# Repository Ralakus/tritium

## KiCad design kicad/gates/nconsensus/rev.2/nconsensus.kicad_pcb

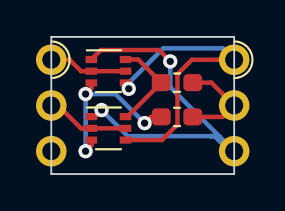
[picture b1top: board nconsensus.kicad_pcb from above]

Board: 2 copper layers, 10.2 x 7.6 mm, 6 parts (0 on the bottom side), 7 nets.

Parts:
J1, J2: Conn_01x03; Edge_Castellation_1x03_P2.54
Q1, Q2: BSS8402DW; SOT-363_SC-70-6
R1, R2: 12k; R_0603_1608Metric_Pad1.05x0.95mm_HandSolder

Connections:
A: J1.1, Q1.2, Q1.5
B: J1.2, Q2.2, Q2.5
unnamed: Q1.3, Q2.3, R1.1
unnamed: Q1.6, Q2.6, R2.2
Out: J2.2, R1.2, R2.1
Vdd: J2.1, Q1.4, Q2.4
Vss: J2.3, Q1.1, Q2.1

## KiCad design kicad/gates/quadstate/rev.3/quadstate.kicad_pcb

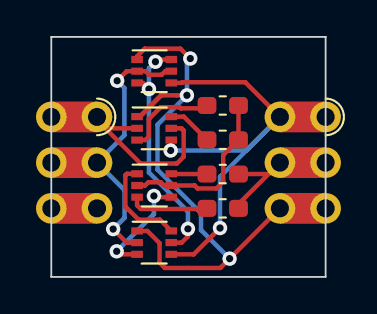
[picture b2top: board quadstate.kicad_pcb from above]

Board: 2 copper layers, 15.2 x 13.3 mm, 10 parts (0 on the bottom side), 13 nets.

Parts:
J1, J2: Conn_01x03; Hybrid_Castellation_1x03_P2.54
Q1, Q2, Q3, Q4: BSS8402DW; SOT-363_SC-70-6
R1, R2, R3, R4: 12k; R_0603_1608Metric_Pad1.05x0.95mm_HandSolder

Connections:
Gate: J1.2, Q1.2, Q1.5, Q2.2
In: J1.1, Q3.2, Q3.5
unnamed: Q1.3, Q1.6, Q2.5
unnamed: Q2.3, Q4.4
unnamed: Q2.6, Q4.1
unnamed: Q3.3, R1.1
unnamed: Q3.6, R2.2
unnamed: Q4.2, Q4.5, R1.2, R2.1
unnamed: Q4.3, R3.1
unnamed: Q4.6, R4.2
Out: J2.2, R3.2, R4.1
Vdd: J2.1, Q1.4, Q2.4, Q3.4
Vss: J2.3, Q1.1, Q2.1, Q3.1

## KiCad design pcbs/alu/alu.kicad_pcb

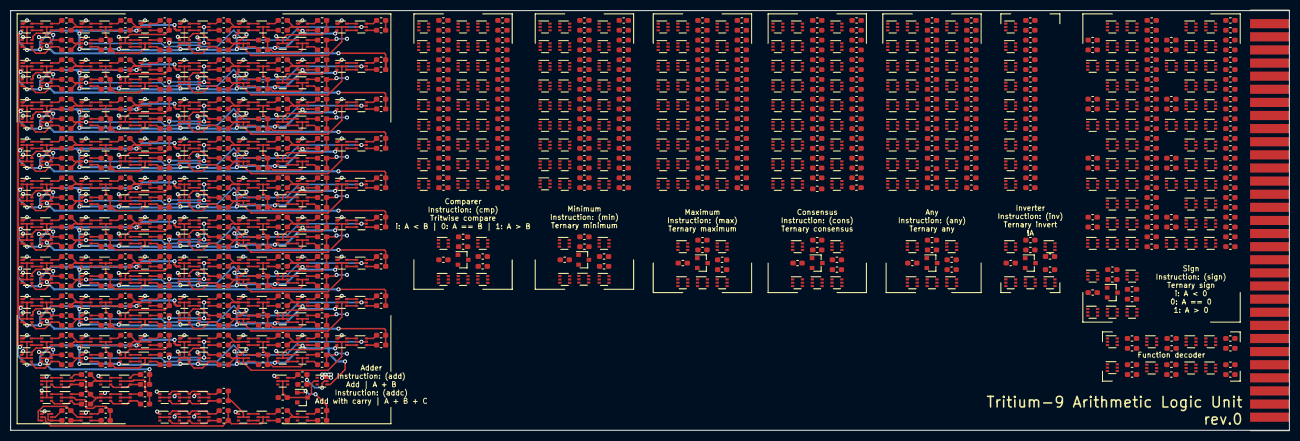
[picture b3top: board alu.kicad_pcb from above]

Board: 2 copper layers, 247.7 x 81.3 mm, 1037 parts (0 on the bottom side), 1030 nets.

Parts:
J1: Conn_02x31_Top_Bottom; BUS_AT_8bit
Q1, Q2, Q3, Q4, Q5, Q6, Q7, Q8, Q9, Q10, Q11, Q12, Q13, Q14, Q15, Q16, Q17, Q18, Q19, Q20, Q21, Q22, Q23, Q24, Q25, Q26, Q27, Q28, Q29, Q30, Q31, Q32, Q33, Q34, Q35, Q36, Q37, Q38, Q39, Q40, Q41, Q42, Q43, Q44, Q45, Q46, Q47, Q48, Q49, Q50, Q51, Q52, Q53, Q54, Q55, Q56, Q57, Q58, Q59, Q60, Q61, Q62, Q63, Q64, Q65, Q66, Q67, Q68, Q69, Q70, Q71, Q72, Q73, Q74, Q75, Q76, Q77, Q78, Q79, Q80, Q81, Q82, Q83, Q84, Q85, Q86, Q87, Q88, Q89, Q90, Q91, Q92, Q93, Q94, Q95, Q96, Q97, Q98, Q99, Q100, Q101, Q102, Q103, Q104, Q105, Q106, Q107, Q108, Q109, Q110, Q111, Q112, Q113, Q114, Q115, Q116, Q117, Q118, Q119, Q120, Q121, Q122, Q123, Q124, Q125, Q126, Q127, Q128, Q129, Q130, Q131, Q132, Q133, Q134, Q135, Q136, Q137, Q138, Q139, Q140, Q141, Q142, Q143, Q144, Q145, Q146, Q147, Q148, Q149, Q150, Q151, Q152, Q153, Q154, Q155, Q156, Q157, Q158, Q159, Q160, Q161, Q162, Q163, Q164, Q165, Q166, Q167, Q168, Q169, Q170, Q171, Q172, Q173, Q174, Q175, Q176, Q177, Q178, Q179, Q180, Q181, Q182, Q183, Q184, Q185, Q186, Q187, Q188, Q189, Q190, Q191, Q192, Q193, Q194, Q195, Q196, Q197, Q198, Q199, Q200, Q201, Q202, Q203, Q204, Q205, Q206, Q207, Q208, Q209, Q210, Q211, Q212, Q213, Q214, Q215, Q216, Q217, Q218, Q219, Q220, Q221, Q222, Q223, Q224, Q225, Q226, Q227, Q228, Q229, Q230, Q231, Q232, Q233, Q234, Q235, Q236, Q237, Q238, Q239, Q240, Q241, Q242, Q243, Q244, Q245, Q246, Q247, Q248, Q249, Q250, Q251, Q252, Q253, Q254, Q255, Q256, Q257, Q258, Q259, Q260, Q261, Q262, Q263, Q264, Q265, Q266, Q267, Q268, Q269, Q270, Q271, Q272, Q273, Q274, Q275, Q276, Q277, Q278, Q279, Q280, Q281, Q282, Q283, Q284, Q285, Q286, Q287, Q288, Q289, Q290, Q291, Q292, Q293, Q294, Q295, Q296, Q297, Q298, Q299, Q300, Q301, Q302, Q303, Q304, Q305, Q306, Q307, Q308, Q309, Q310, Q311, Q312, Q313, Q314, Q315, Q316, Q317, Q318, Q319, Q320, Q321, Q322, Q323, Q324, Q325, Q326, Q327, Q328, Q329, Q330, Q331, Q332, Q333, Q334, Q335, Q336, Q337, Q338, Q339, Q340, Q341, Q342, Q343, Q344, Q345, Q346, Q347, Q348, Q349, Q350, Q351, Q352, Q353, Q354, Q355, Q356, Q357, Q358, Q359, Q360, Q361, Q362, Q363, Q364, Q365, Q366, Q367, Q368, Q369, Q370, Q371, Q372, Q373, Q374, Q375, Q376, Q377, Q378, Q379, Q380, Q381, Q382, Q383, Q384, Q385, Q386, Q387, Q388, Q389, Q390, Q391, Q392, Q393, Q394, Q395, Q396, Q397, Q398, Q399, Q400, Q401, Q402, Q403, Q404, Q405, Q406, Q407, Q408, Q409, Q410, Q411, Q412, Q413, Q414, Q415, Q416, Q417, Q418, Q419, Q420, Q421, Q422, Q424, Q425, Q426, Q428, Q429, Q430, Q432, Q433, Q434, Q436, Q437, Q438, Q440, Q441, Q442, Q444, Q445, Q446, Q448, Q449, Q450, Q452, Q453, Q454, Q455, Q456, Q457, Q458, Q459, Q460, Q461, Q462, Q463, Q464, Q465, Q466, Q467, Q468, Q469, Q470: BSS8402DW; SOT-363_SC-70-6
Q423, Q427, Q431, Q435, Q439, Q443, Q447, Q451: 2N7002; SOT-23
R2, R3, R4, R5, R6, R7, R8, R9, R10, R11, R12, R13, R14, R15, R16, R17, R18, R19, R20, R21, R22, R23, R24, R25, R26, R27, R28, R29, R30, R31, R32, R33, R34, R35, R36, R37, R38, R39, R40, R41, R42, R43, R44, R45, R46, R47, R48, R49, R50, R51, R52, R53, R54, R55, R56, R57, R58, R59, R60, R61, R62, R63, R64, R65, R66, R67, R68, R69, R70, R71, R72, R73, R74, R75, R76, R77, R78, R79, R80, R81, R82, R83, R84, R85, R86, R87, R88, R89, R90, R91, R92, R93, R94, R95, R96, R97, R98, R99, R100, R101, R102, R103, R104, R105, R106, R107, R108, R109, R110, R111, R112, R113, R114, R115, R116, R117, R118, R119, R120, R121, R122, R123, R124, R125, R126, R127, R128, R129, R130, R131, R132, R133, R134, R135, R136, R137, R138, R139, R140, R141, R142, R143, R144, R145, R146, R147, R148, R149, R150, R151, R152, R153, R154, R155, R156, R157, R158, R159, R160, R161, R162, R163, R164, R165, R166, R167, R168, R169, R170, R171, R172, R173, R174, R175, R176, R177, R178, R179, R180, R181, R182, R183, R184, R185, R186, R187, R188, R189, R190, R191, R192, R193, R194, R195, R196, R197, R198, R199, R200, R201, R202, R203, R204, R205, R206, R207, R208, R209, R210, R211, R212, R213, R214, R215, R216, R217, R218, R219, R220, R221, R222, R223, R224, R225, R226, R227, R228, R229, R230, R231, R232, R233, R234, R235, R236, R237, R238, R239, R240, R241, R242, R243, R244, R245, R246, R247, R248, R249, R250, R251, R252, R253, R254, R255, R256, R257, R258, R259, R260, R261, R262, R263, R264, R265, R266, R267, R268, R269, R270, R271, R272, R273, R274, R275, R276, R277, R278, R279, R280, R281, R282, R283, R284, R285, R286, R287, R288, R289, R290, R291, R292, R293, R294, R295, R296, R297, R298, R299, R300, R301, R302, R303, R304, R305, R306, R307, R308, R309, R310, R311, R312, R313, R314, R315, R316, R317, R318, R319, R320, R321, R322, R323, R324, R325, R326, R327, R328, R329, R330, R331, R332, R333, R334, R335, R336, R337, R338, R339, R340, R341, R342, R343, R344, R345, R346, R347, R348, R349, R350, R351, R352, R353, R354, R355, R356, R357, R358, R359, R360, R361, R362, R363, R364, R365, R366, R367, R368, R369, R370, R371, R372, R373, R374, R375, R376, R377, R378, R379, R380, R381, R382, R383, R384, R385, R386, R387, R388, R389, R390, R391, R392, R393, R394, R395, R396, R397, R398, R399, R400, R401, R402, R403, R404, R405, R406, R407, R408, R409, R410, R411, R412, R413, R414, R415, R416, R417, R418, R419, R420, R421, R422, R423, R424, R425, R426, R427, R428, R429, R430, R431, R432, R433, R434, R435, R436, R437, R438, R439, R440, R441, R442, R443, R444, R445, R446, R447, R448, R449, R450, R451, R452, R453, R454, R455, R456, R457, R458, R459, R460, R461, R462, R463, R464, R465, R466, R467, R468, R469, R470, R471, R472, R473, R474, R475, R476, R477, R478, R479, R480, R481, R482, R483, R484, R485, R486, R487, R488, R489, R490, R491, R492, R493, R494, R495, R496, R497, R498, R499, R500, R501, R502, R503, R504, R505, R506, R507, R508, R517, R518, R519, R520, R521, R522, R523, R524, R525, R526, R527, R528, R529, R530, R531, R532, R533, R534, R535, R536, R537, R538, R539, R540, R541, R542, R543, R544, R545, R546, R547, R548, R549, R550, R551, R552, R553, R554, R555, R556, R557, R558, R560, R561, R562, R563, R564, R565, R566, R567, R568, R569, R570, R571, R572, R573, R574, R575: 12k; R_0603_1608Metric_Pad1.05x0.95mm_HandSolder
R559: 470k; R_0603_1608Metric_Pad1.05x0.95mm_HandSolder

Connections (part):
/FnA0: Q5.6, Q417.2, Q417.5, Q454.2, Q454.5, Q456.2, Q456.5, Q458.2, Q458.5, R439.1
/FnA1: Q460.2, Q460.5, Q462.2, Q462.5, Q464.2, Q464.5, R528.1, R529.2
/FnA2: Q412.2, Q412.5, Q466.2, Q466.5, Q468.2, Q468.5, Q470.2, Q470.5, R452.1, R517.2
/FnB0: Q4.6, Q416.2, Q416.5, Q421.2, Q421.5, Q433.2, Q433.5, Q445.2, Q445.5, R5.1
/FnB1: Q425.2, Q425.5, Q437.2, Q437.5, Q449.2, Q449.5, R526.1, R527.2
/FnB2: Q411.2, Q411.5, Q429.2, Q429.5, Q441.2, Q441.5, Q453.2, Q453.5, R450.1, R451.2
/adder/CarryIn: Q12.2, Q12.5, Q15.2, Q15.5, R530.1, R531.2
/adder/Vdd: Q6.3, Q7.3, Q8.3, Q9.3, Q10.3, Q11.3, Q12.3, Q13.3, Q14.3, Q18.3, Q19.3, Q20.3, Q21.3, Q22.3, Q23.3, Q27.3, Q28.3, Q29.3, Q30.3, Q31.3, Q32.3, Q36.3, Q37.3, Q38.3, Q39.3, Q40.3, Q41.3, Q42.3, Q43.3, Q44.3, Q48.3, Q49.3, Q50.3, Q51.3, Q52.3, Q53.3, Q57.3, Q58.3, Q59.3, Q60.3, Q61.3, Q62.3, Q66.3, Q67.3, Q68.3, Q72.3, Q73.3, Q74.3, Q75.3, Q76.3, Q77.3, Q78.3, Q79.3, Q80.3, Q84.3, Q85.3, Q86.3, Q87.3, Q88.3, Q89.3, Q93.3, Q94.3, Q95.3, Q96.3, Q97.3, Q98.3, Q102.3, Q103.3, Q104.3, Q105.3, Q106.3, Q107.3, Q108.3, Q109.3, Q110.3, Q114.3, Q115.3, Q116.3, Q117.3, Q118.3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
/adder/Vss: Q6.1, Q7.1, Q8.1, Q9.1, Q10.1, Q11.1, Q12.1, Q13.1, Q14.1, Q18.1, Q19.1, Q20.1, Q21.1, Q22.1, Q23.1, Q27.1, Q28.1, Q29.1, Q30.1, Q31.1, Q32.1, Q36.1, Q37.1, Q38.1, Q39.1, Q40.1, Q41.1, Q42.1, Q43.1, Q44.1, Q48.1, Q49.1, Q50.1, Q51.1, Q52.1, Q53.1, Q57.1, Q58.1, Q59.1, Q60.1, Q61.1, Q62.1, Q66.1, Q67.1, Q68.1, Q72.1, Q73.1, Q74.1, Q75.1, Q76.1, Q77.1, Q78.1, Q79.1, Q80.1, Q84.1, Q85.1, Q86.1, Q87.1, Q88.1, Q89.1, Q93.1, Q94.1, Q95.1, Q96.1, Q97.1, Q98.1, Q102.1, Q103.1, Q104.1, Q105.1, Q106.1, Q107.1, Q108.1, Q109.1, Q110.1, Q114.1, Q115.1, Q116.1, Q117.1, Q118.1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
/any/Vdd: Q312.3, Q314.3, Q315.3, Q317.3, Q318.3, Q320.3, Q321.3, Q323.3, Q324.3, Q326.3, Q327.3, Q329.3, Q330.3, Q332.3, Q333.3, Q335.3, Q336.3, Q338.3, Q442.4
/any/Vss: Q312.1, Q314.1, Q315.1, Q317.1, Q318.1, Q320.1, Q321.1, Q323.1, Q324.1, Q326.1, Q327.1, Q329.1, Q330.1, Q332.1, Q333.1, Q335.1, Q336.1, Q338.1, Q442.6
/compare/Vdd: Q258.3, Q259.3, Q260.3, Q261.3, Q262.3, Q263.3, Q264.3, Q265.3, Q266.3, Q267.3, Q268.3, Q269.3, Q270.3, Q271.3, Q272.3, Q273.3, Q274.3, Q275.3, Q276.3, Q277.3, Q278.3, Q279.3, Q280.3, Q281.3, Q282.3, Q283.3, Q284.3, Q426.4
/compare/Vss: Q258.1, Q259.1, Q260.1, Q261.1, Q262.1, Q263.1, Q264.1, Q265.1, Q266.1, Q267.1, Q268.1, Q269.1, Q270.1, Q271.1, Q272.1, Q273.1, Q274.1, Q275.1, Q276.1, Q277.1, Q278.1, Q279.1, Q280.1, Q281.1, Q282.1, Q283.1, Q284.1, Q426.6
/consensus/Vdd: Q285.3, Q286.3, Q287.3, Q288.3, Q289.3, Q290.3, Q291.3, Q292.3, Q293.3, Q294.3, Q295.3, Q296.3, Q297.3, Q298.3, Q299.3, Q300.3, Q301.3, Q302.3, Q303.3, Q304.3, Q305.3, Q306.3, Q307.3, Q308.3, Q309.3, Q310.3, Q311.3, Q438.4
/consensus/Vss: Q285.1, Q286.1, Q287.1, Q288.1, Q289.1, Q290.1, Q291.1, Q292.1, Q293.1, Q294.1, Q295.1, Q296.1, Q297.1, Q298.1, Q299.1, Q300.1, Q301.1, Q302.1, Q303.1, Q304.1, Q305.1, Q306.1, Q307.1, Q308.1, Q309.1, Q310.1, Q311.1, Q438.6
/inverter/Vdd: Q339.3, Q340.3, Q341.3, Q342.3, Q343.3, Q344.3, Q345.3, Q346.3, Q347.3, Q446.4
/inverter/Vss: Q339.1, Q340.1, Q341.1, Q342.1, Q343.1, Q344.1, Q345.1, Q346.1, Q347.1, Q446.6
/max/Vdd: Q231.3, Q233.3, Q234.3, Q236.3, Q237.3, Q239.3, Q240.3, Q242.3, Q243.3, Q245.3, Q246.3, Q248.3, Q249.3, Q251.3, Q252.3, Q254.3, Q255.3, Q257.3, Q434.4
/max/Vss: Q231.1, Q232.1, Q233.1, Q234.1, Q235.1, Q236.1, Q237.1, Q238.1, Q239.1, Q240.1, Q241.1, Q242.1, Q243.1, Q244.1, Q245.1, Q246.1, Q247.1, Q248.1, Q249.1, Q250.1, Q251.1, Q252.1, Q253.1, Q254.1, Q255.1, Q256.1, Q257.1, Q434.6
/min/Vdd: Q204.3, Q205.3, Q206.3, Q207.3, Q208.3, Q209.3, Q210.3, Q211.3, Q212.3, Q213.3, Q214.3, Q215.3, Q216.3, Q217.3, Q218.3, Q219.3, Q220.3, Q221.3, Q222.3, Q223.3, Q224.3, Q225.3, Q226.3, Q227.3, Q228.3, Q229.3, Q230.3, Q430.4
/min/Vss: Q204.1, Q206.1, Q207.1, Q209.1, Q210.1, Q212.1, Q213.1, Q215.1, Q216.1, Q218.1, Q219.1, Q221.1, Q222.1, Q224.1, Q225.1, Q227.1, Q228.1, Q230.1, Q430.6
/sign/Vdd: Q351.3, Q352.3, Q353.3, Q354.3, Q356.3, Q357.3, Q358.3, Q359.3, Q360.3, Q361.3, Q362.3, Q363.3, Q365.3, Q366.3, Q367.3, Q368.3, Q373.3, Q374.3, Q375.3, Q376.3, Q381.3, Q382.3, Q383.3, Q384.3, Q385.3, Q386.3, Q387.3, Q388.3, Q391.3, Q392.3, Q395.3, Q396.3, Q397.3, Q398.3, Q400.3, Q402.3, Q403.3, Q404.3, Q405.3, Q407.3, Q450.4
/sign/Vss: Q351.1, Q352.1, Q353.1, Q354.1, Q356.1, Q357.1, Q358.1, Q359.1, Q360.1, Q361.1, Q362.1, Q363.1, Q365.1, Q366.1, Q367.1, Q368.1, Q373.1, Q374.1, Q375.1, Q376.1, Q381.1, Q382.1, Q383.1, Q384.1, Q385.1, Q386.1, Q387.1, Q388.1, Q391.1, Q392.1, Q395.1, Q396.1, Q397.1, Q398.1, Q400.1, Q402.1, Q403.1, Q404.1, Q405.1, Q407.1, Q450.6
A0: J1.40, Q6.2, Q6.5, Q7.2, Q7.5, Q230.2, Q230.5, Q257.2, Q257.5, Q283.2, Q283.5, Q311.2, Q311.5, Q338.2, Q338.5, Q347.2, Q347.5, Q402.2, Q402.5, Q406.2, Q406.5
A1: J1.39, Q72.2, Q72.5, Q73.2, Q73.5, Q227.2, Q227.5, Q254.2, Q254.5, Q280.2, Q280.5, Q308.2, Q308.5, Q335.2, Q335.5, Q346.2, Q346.5, Q354.2, Q354.5, Q372.2, Q372.5
A2: J1.38, Q138.2, Q138.5, Q139.2, Q139.5, Q224.2, Q224.5, Q251.2, Q251.5, Q277.2, Q277.5, Q305.2, Q305.5, Q332.2, Q332.5, Q345.2, Q345.5, Q362.2, Q362.5, Q368.2, Q368.5
A3: J1.37, Q8.2, Q8.5, Q9.2, Q9.5, Q221.2, Q221.5, Q248.2, Q248.5, Q274.2, Q274.5, Q302.2, Q302.5, Q329.2, Q329.5, Q344.2, Q344.5, Q353.2, Q353.5, Q371.2, Q371.5
A4: J1.36, Q74.2, Q74.5, Q75.2, Q75.5, Q218.2, Q218.5, Q245.2, Q245.5, Q271.2, Q271.5, Q299.2, Q299.5, Q326.2, Q326.5, Q343.2, Q343.5, Q360.2, Q360.5, Q367.2, Q367.5
A5: J1.35, Q140.2, Q140.5, Q141.2, Q141.5, Q215.2, Q215.5, Q242.2, Q242.5, Q268.2, Q268.5, Q296.2, Q296.5, Q323.2, Q323.5, Q342.2, Q342.5, Q352.2, Q352.5, Q370.2, Q370.5
A6: J1.34, Q10.2, Q10.5, Q11.2, Q11.5, Q212.2, Q212.5, Q239.2, Q239.5, Q265.2, Q265.5, Q293.2, Q293.5, Q320.2, Q320.5, Q341.2, Q341.5, Q358.2, Q358.5, Q366.2, Q366.5
A7: J1.33, Q76.2, Q76.5, Q77.2, Q77.5, Q209.2, Q209.5, Q236.2, Q236.5, Q262.2, Q262.5, Q290.2, Q290.5, Q317.2, Q317.5, Q340.2, Q340.5, Q351.2, Q351.5, Q369.2, Q369.5
A8: J1.32, Q142.2, Q142.5, Q143.2, Q143.5, Q206.2, Q206.5, Q233.2, Q233.5, Q259.2, Q259.5, Q287.2, Q287.5, Q314.2, Q314.5, Q339.2, Q339.5, Q356.2, Q356.5, Q365.2, Q365.5
B0: J1.49, Q36.2, Q36.5, Q37.2, Q37.5, Q229.2, Q229.5, Q256.2, Q256.5, Q284.2, Q284.5, Q310.2, Q310.5, Q337.2, Q337.5
B1: J1.48, Q102.2, Q102.5, Q103.2, Q103.5, Q226.2, Q226.5, Q253.2, Q253.5, Q281.2, Q281.5, Q307.2, Q307.5, Q334.2, Q334.5
B2: J1.47, Q168.2, Q168.5, Q169.2, Q169.5, Q223.2, Q223.5, Q250.2, Q250.5, Q278.2, Q278.5, Q304.2, Q304.5, Q331.2, Q331.5
B3: J1.46, Q38.2, Q38.5, Q39.2, Q39.5, Q220.2, Q220.5, Q247.2, Q247.5, Q275.2, Q275.5, Q301.2, Q301.5, Q328.2, Q328.5
B4: J1.45, Q104.2, Q104.5, Q105.2, Q105.5, Q217.2, Q217.5, Q244.2, Q244.5, Q272.2, Q272.5, Q298.2, Q298.5, Q325.2, Q325.5
B5: J1.44, Q170.2, Q170.5, Q171.2, Q171.5, Q214.2, Q214.5, Q241.2, Q241.5, Q269.2, Q269.5, Q295.2, Q295.5, Q322.2, Q322.5
B6: J1.43, Q40.2, Q40.5, Q41.2, Q41.5, Q211.2, Q211.5, Q238.2, Q238.5, Q266.2, Q266.5, Q292.2, Q292.5, Q319.2, Q319.5
B7: J1.42, Q106.2, Q106.5, Q107.2, Q107.5, Q208.2, Q208.5, Q235.2, Q235.5, Q263.2, Q263.5, Q289.2, Q289.5, Q316.2, Q316.5
B8: J1.41, Q172.2, Q172.5, Q173.2, Q173.5, Q205.2, Q205.5, Q232.2, Q232.5, Q260.2, Q260.5, Q286.2, Q286.5, Q313.2, Q313.5
CarryIn: J1.30, Q3.2, Q3.5, Q355.2, Q355.5
CarryOut: J1.31, R239.1, R240.2
Fn0: J1.58, Q4.2, Q4.5
Fn1: J1.57, Q5.2, Q5.5
GND: J1.20, J1.51, Q1.5, Q423.2, Q427.2, Q431.2, Q435.2, Q439.2, Q443.2, Q447.2, Q451.2, R559.1
unnamed: Q1.2, Q414.2, Q414.5, R535.1, R536.2
unnamed: Q1.3, Q2.2, Q2.5, R559.2
unnamed: Q1.4, Q1.6, R558.1
unnamed: Q2.4, R2.2
unnamed: Q2.6, R3.1
unnamed: Q3.4, Q348.4, R440.2
unnamed: Q3.6, Q348.1
unnamed: Q10.4, Q17.3
unnamed: Q10.6, Q17.1
unnamed: Q11.4, Q14.4, R11.2
unnamed: Q11.6, Q14.6, R12.1
unnamed: Q7.4, Q12.4, R7.2
unnamed: Q7.6, Q12.6, R8.1
unnamed: Q13.2, Q13.5, Q16.2, Q16.5, R235.1, R236.2
unnamed: Q9.4, Q13.4, R9.2
unnamed: Q9.6, Q13.6, R10.1
unnamed: Q14.2, Q14.5, Q17.2, Q17.5, R237.1, R238.2
unnamed: Q6.6, Q15.1
unnamed: Q6.4, Q15.3
unnamed: Q15.4, R13.2
unnamed: Q15.6, R14.1
unnamed: Q8.6, Q16.1
unnamed: Q8.4, Q16.3
unnamed: Q16.4, R15.2
unnamed: Q16.6, R16.1
unnamed: Q17.4, R17.2
unnamed: Q17.6, R18.1
unnamed: Q18.2, Q18.5, Q69.2, Q69.5, R7.1, R8.2
unnamed: Q18.4, R19.2
unnamed: Q18.6, R20.1
unnamed: Q19.2, Q19.5, Q70.2, Q70.5, R9.1, R10.2
unnamed: Q19.4, R21.2
unnamed: Q19.6, R22.1
unnamed: Q20.2, Q20.5, Q71.2, Q71.5, R11.1, R12.2
unnamed: Q20.4, R23.2
unnamed: Q20.6, R24.1
unnamed: Q21.2, Q21.5, R13.1, R14.2
unnamed: Q21.4, Q24.3
unnamed: Q21.6, Q24.1
unnamed: Q22.2, Q22.5, R15.1, R16.2
unnamed: Q22.4, Q25.3
unnamed: Q22.6, Q25.1
unnamed: Q23.2, Q23.5, R17.1, R18.2
unnamed: Q23.4, Q26.3
unnamed: Q23.6, Q26.1
unnamed: Q24.2, Q24.5, Q33.2, Q33.5, R19.1, R20.2
unnamed: Q24.4, R25.2
unnamed: Q24.6, R26.1
unnamed: Q25.2, Q25.5, Q34.2, Q34.5, R21.1, R22.2
unnamed: Q25.4, R27.2
unnamed: Q25.6, R28.1
unnamed: Q26.2, Q26.5, Q35.2, Q35.5, R23.1, R24.2
unnamed: Q26.4, R29.2
unnamed: Q26.6, R30.1
unnamed: Q27.2, Q27.5, R25.1, R26.2
unnamed: Q27.4, R31.2
unnamed: Q27.6, R32.1
unnamed: Q28.2, Q28.5, R27.1, R28.2
unnamed: Q28.4, R33.2
unnamed: Q28.6, R34.1
unnamed: Q29.2, Q29.5, R29.1, R30.2
unnamed: Q29.4, R35.2
unnamed: Q29.6, R36.1
unnamed: Q30.2, Q30.5, R31.1, R32.2
unnamed: Q30.4, Q33.3
unnamed: Q30.6, Q33.1
unnamed: Q31.2, Q31.5, R33.1, R34.2
unnamed: Q31.4, Q34.3
unnamed: Q31.6, Q34.1
unnamed: Q32.2, Q32.5, R35.1, R36.2
unnamed: Q32.4, Q35.3
unnamed: Q32.6, Q35.1
unnamed: Q33.4, R37.2
unnamed: Q33.6, R38.1
unnamed: Q34.4, R39.2
unnamed: Q34.6, R40.1
unnamed: Q35.4, R41.2
unnamed: Q35.6, R42.1
unnamed: Q36.4, Q45.3
unnamed: Q36.6, Q45.1
unnamed: Q37.4, Q42.4, R43.2
unnamed: Q37.6, Q42.6, R44.1
unnamed: Q38.4, Q46.3
unnamed: Q38.6, Q46.1
unnamed: Q39.4, Q43.4, R45.2
unnamed: Q39.6, Q43.6, R46.1
unnamed: Q40.4, Q47.3
unnamed: Q40.6, Q47.1
unnamed: Q41.4, Q44.4, R47.2
unnamed: Q41.6, Q44.6, R48.1
unnamed: Q42.2, Q42.5, Q45.2, Q45.5, R37.1, R38.2
unnamed: Q43.2, Q43.5, Q46.2, Q46.5, R39.1, R40.2
unnamed: Q44.2, Q44.5, Q47.2, Q47.5, R41.1, R42.2
unnamed: Q45.4, R49.2
unnamed: Q45.6, R50.1
unnamed: Q46.4, R51.2
unnamed: Q46.6, R52.1
unnamed: Q47.4, R53.2
unnamed: Q47.6, R54.1
unnamed: Q48.2, Q48.5, Q66.2, Q66.5, R43.1, R44.2
unnamed: Q48.4, R55.2
unnamed: Q48.6, R56.1
unnamed: Q49.2, Q49.5, Q67.2, Q67.5, R45.1, R46.2
unnamed: Q49.4, R57.2
unnamed: Q49.6, R58.1
unnamed: Q50.2, Q50.5, Q68.2, Q68.5, R47.1, R48.2
unnamed: Q50.4, R59.2
unnamed: Q50.6, R60.1
unnamed: Q51.2, Q51.5, R49.1, R50.2
unnamed: Q51.4, Q54.3
unnamed: Q51.6, Q54.1
unnamed: Q52.2, Q52.5, R51.1, R52.2
unnamed: Q52.4, Q55.3
unnamed: Q52.6, Q55.1
unnamed: Q53.2, Q53.5, R53.1, R54.2
unnamed: Q53.4, Q56.3
unnamed: Q53.6, Q56.1
unnamed: Q54.2, Q54.5, Q63.2, Q63.5, R55.1, R56.2
unnamed: Q54.4, R61.2
unnamed: Q54.6, R62.1
unnamed: Q55.2, Q55.5, Q64.2, Q64.5, R57.1, R58.2
unnamed: Q55.4, R63.2
unnamed: Q55.6, R64.1
unnamed: Q56.2, Q56.5, Q65.2, Q65.5, R59.1, R60.2
unnamed: Q56.4, R65.2
unnamed: Q56.6, R66.1
unnamed: Q57.2, Q57.5, R61.1, R62.2
unnamed: Q57.4, R67.2
unnamed: Q57.6, R68.1
unnamed: Q58.2, Q58.5, R63.1, R64.2
unnamed: Q58.4, R69.2
unnamed: Q58.6, R70.1
unnamed: Q59.2, Q59.5, R65.1, R66.2
unnamed: Q59.4, R71.2
unnamed: Q59.6, R72.1
unnamed: Q60.2, Q60.5, R67.1, R68.2
unnamed: Q60.4, Q63.3
unnamed: Q60.6, Q63.1
unnamed: Q61.2, Q61.5, R69.1, R70.2
unnamed: Q61.4, Q64.3
unnamed: Q61.6, Q64.1
unnamed: Q62.2, Q62.5, R71.1, R72.2
unnamed: Q62.4, Q65.3
unnamed: Q62.6, Q65.1
unnamed: Q63.4, R73.2
unnamed: Q63.6, R74.1
unnamed: Q64.4, R75.2
unnamed: Q64.6, R76.1
unnamed: Q65.4, R77.2
unnamed: Q65.6, R78.1
unnamed: Q66.4, Q69.3
unnamed: Q66.6, Q69.1
unnamed: Q67.4, Q70.3
unnamed: Q67.6, Q70.1
unnamed: Q68.4, Q71.3
unnamed: Q68.6, Q71.1
unnamed: Q69.4, R79.2
unnamed: Q69.6, R80.1
unnamed: Q70.4, R81.2
unnamed: Q70.6, R82.1
unnamed: Q71.4, R83.2
unnamed: Q71.6, R84.1
unnamed: Q72.4, Q81.3
unnamed: Q72.6, Q81.1
unnamed: Q73.4, Q78.4, R85.2
unnamed: Q73.6, Q78.6, R86.1
unnamed: Q74.4, Q82.3
unnamed: Q74.6, Q82.1
unnamed: Q75.4, Q79.4, R87.2
unnamed: Q75.6, Q79.6, R88.1
unnamed: Q76.4, Q83.3
unnamed: Q76.6, Q83.1
unnamed: Q77.4, Q80.4, R89.2
unnamed: Q77.6, Q80.6, R90.1
unnamed: Q78.2, Q78.5, Q81.2, Q81.5, R79.1, R80.2
unnamed: Q79.2, Q79.5, Q82.2, Q82.5, R81.1, R82.2
unnamed: Q80.2, Q80.5, Q83.2, Q83.5, R83.1, R84.2
unnamed: Q81.4, R91.2
unnamed: Q81.6, R92.1
unnamed: Q82.4, R93.2
unnamed: Q82.6, R94.1
unnamed: Q83.4, R95.2
unnamed: Q83.6, R96.1
unnamed: Q84.4, R97.2
unnamed: Q84.6, R98.1
unnamed: Q85.4, R99.2
unnamed: Q85.6, R100.1
unnamed: Q86.4, R101.2
unnamed: Q86.6, R102.1
unnamed: Q87.2, Q87.5, R91.1, R92.2
unnamed: Q87.4, Q90.3
unnamed: Q87.6, Q90.1
unnamed: Q88.2, Q88.5, R93.1, R94.2
unnamed: Q88.4, Q91.3
unnamed: Q88.6, Q91.1
unnamed: Q89.2, Q89.5, R95.1, R96.2
unnamed: Q89.4, Q92.3
unnamed: Q89.6, Q92.1
unnamed: Q90.2, Q90.5, Q99.2, Q99.5, R97.1, R98.2
unnamed: Q90.4, R103.2
unnamed: Q90.6, R104.1
unnamed: Q91.4, R105.2
unnamed: Q91.6, R106.1
unnamed: Q92.4, R107.2
unnamed: Q92.6, R108.1
unnamed: Q93.2, Q93.5, R103.1, R104.2
unnamed: Q93.4, R109.2
unnamed: Q93.6, R110.1
unnamed: Q94.2, Q94.5, R105.1, R106.2
unnamed: Q94.4, R111.2
unnamed: Q94.6, R112.1
unnamed: Q95.2, Q95.5, R107.1, R108.2
unnamed: Q95.4, R113.2
unnamed: Q95.6, R114.1
unnamed: Q96.2, Q96.5, R109.1, R110.2
unnamed: Q96.4, Q99.3
unnamed: Q96.6, Q99.1
unnamed: Q97.2, Q97.5, R111.1, R112.2
unnamed: Q98.2, Q98.5, R113.1, R114.2
unnamed: Q99.4, R115.2
unnamed: Q99.6, R116.1
unnamed: Q97.6, Q100.1
unnamed: Q91.2, Q91.5, Q100.2, Q100.5, R99.1, R100.2
unnamed: Q97.4, Q100.3
unnamed: Q100.4, R117.2
unnamed: Q100.6, R118.1
unnamed: Q98.6, Q101.1
unnamed: Q92.2, Q92.5, Q101.2, Q101.5, R101.1, R102.2
unnamed: Q98.4, Q101.3
unnamed: Q101.4, R119.2
unnamed: Q101.6, R120.1
unnamed: Q102.4, Q111.3
unnamed: Q102.6, Q111.1
unnamed: Q103.4, Q108.4, R121.2
unnamed: Q103.6, Q108.6, R122.1
unnamed: Q104.4, Q112.3
unnamed: Q104.6, Q112.1
unnamed: Q105.4, Q109.4, R123.2
unnamed: Q105.6, Q109.6, R124.1
unnamed: Q106.4, Q113.3
unnamed: Q106.6, Q113.1
unnamed: Q107.4, Q110.4, R125.2
unnamed: Q107.6, Q110.6, R126.1
unnamed: Q108.2, Q108.5, Q111.2, Q111.5, R115.1, R116.2
unnamed: Q109.2, Q109.5, Q112.2, Q112.5, R117.1, R118.2
unnamed: Q110.2, Q110.5, Q113.2, Q113.5, R119.1, R120.2
unnamed: Q111.4, R127.2
unnamed: Q111.6, R128.1
unnamed: Q112.4, R129.2
unnamed: Q112.6, R130.1
unnamed: Q113.4, R131.2
unnamed: Q113.6, R132.1
unnamed: Q114.2, Q114.5, Q132.2, Q132.5, R121.1, R122.2
unnamed: Q114.4, R133.2
unnamed: Q114.6, R134.1
unnamed: Q115.2, Q115.5, Q133.2, Q133.5, R123.1, R124.2
unnamed: Q115.4, R135.2
unnamed: Q115.6, R136.1
unnamed: Q116.2, Q116.5, Q134.2, Q134.5, R125.1, R126.2
unnamed: Q116.4, R137.2
unnamed: Q116.6, R138.1
unnamed: Q117.2, Q117.5, R127.1, R128.2
unnamed: Q117.4, Q120.3
unnamed: Q117.6, Q120.1
unnamed: Q118.2, Q118.5, R129.1, R130.2
unnamed: Q118.4, Q121.3
unnamed: Q118.6, Q121.1
unnamed: Q119.2, Q119.5, R131.1, R132.2
unnamed: Q119.4, Q122.3
unnamed: Q119.6, Q122.1
unnamed: Q120.2, Q120.5, Q129.2, Q129.5, R133.1, R134.2
unnamed: Q120.4, R139.2
unnamed: Q120.6, R140.1
unnamed: Q121.2, Q121.5, Q130.2, Q130.5, R135.1, R136.2
unnamed: Q121.4, R141.2
unnamed: Q121.6, R142.1
unnamed: Q122.2, Q122.5, Q131.2, Q131.5, R137.1, R138.2
unnamed: Q122.4, R143.2
unnamed: Q122.6, R144.1
unnamed: Q123.2, Q123.5, R139.1, R140.2
unnamed: Q123.4, R145.2
unnamed: Q123.6, R146.1
unnamed: Q124.2, Q124.5, R141.1, R142.2
unnamed: Q124.4, R147.2
unnamed: Q124.6, R148.1
unnamed: Q125.2, Q125.5, R143.1, R144.2
unnamed: Q125.4, R149.2
unnamed: Q125.6, R150.1
unnamed: Q126.2, Q126.5, R145.1, R146.2
unnamed: Q126.4, Q129.3
unnamed: Q126.6, Q129.1
unnamed: Q127.2, Q127.5, R147.1, R148.2
unnamed: Q127.4, Q130.3
unnamed: Q127.6, Q130.1
unnamed: Q128.2, Q128.5, R149.1, R150.2
unnamed: Q128.4, Q131.3
unnamed: Q128.6, Q131.1
unnamed: Q129.4, R151.2
unnamed: Q129.6, R152.1
unnamed: Q130.4, R153.2
unnamed: Q130.6, R154.1
unnamed: Q131.4, R155.2
unnamed: Q131.6, R156.1
unnamed: Q132.4, Q135.3
unnamed: Q132.6, Q135.1
unnamed: Q133.4, Q136.3
unnamed: Q133.6, Q136.1
unnamed: Q134.4, Q137.3
unnamed: Q134.6, Q137.1
unnamed: Q84.2, Q84.5, Q135.2, Q135.5, R85.1, R86.2
unnamed: Q135.4, R157.2
unnamed: Q135.6, R158.1
unnamed: Q85.2, Q85.5, Q136.2, Q136.5, R87.1, R88.2
unnamed: Q136.4, R159.2
unnamed: Q136.6, R160.1
unnamed: Q86.2, Q86.5, Q137.2, Q137.5, R89.1, R90.2
unnamed: Q137.4, R161.2
unnamed: Q137.6, R162.1
unnamed: Q138.4, Q147.3
unnamed: Q138.6, Q147.1
unnamed: Q139.4, Q144.4, R163.2
unnamed: Q139.6, Q144.6, R164.1
unnamed: Q140.4, Q148.3
unnamed: Q140.6, Q148.1
unnamed: Q141.4, Q145.4, R165.2
unnamed: Q141.6, Q145.6, R166.1
unnamed: Q142.4, Q149.3
unnamed: Q142.6, Q149.1
unnamed: Q143.4, Q146.4, R167.2
unnamed: Q143.6, Q146.6, R168.1
unnamed: Q144.2, Q144.5, Q147.2, Q147.5, R157.1, R158.2
unnamed: Q145.2, Q145.5, Q148.2, Q148.5, R159.1, R160.2
unnamed: Q146.2, Q146.5, Q149.2, Q149.5, R161.1, R162.2
unnamed: Q147.4, R169.2
unnamed: Q147.6, R170.1
unnamed: Q148.4, R171.2
unnamed: Q148.6, R172.1
unnamed: Q149.4, R173.2
unnamed: Q149.6, R174.1
unnamed: Q150.2, Q150.5, Q201.2, Q201.5, R163.1, R164.2
unnamed: Q150.4, R175.2
unnamed: Q150.6, R176.1
unnamed: Q151.2, Q151.5, Q202.2, Q202.5, R165.1, R166.2
unnamed: Q151.4, R177.2
unnamed: Q151.6, R178.1
unnamed: Q152.2, Q152.5, Q203.2, Q203.5, R167.1, R168.2
unnamed: Q152.4, R179.2
unnamed: Q152.6, R180.1
unnamed: Q153.2, Q153.5, R169.1, R170.2
unnamed: Q153.4, Q156.3
unnamed: Q153.6, Q156.1
unnamed: Q154.2, Q154.5, R171.1, R172.2
unnamed: Q154.4, Q157.3
unnamed: Q154.6, Q157.1
unnamed: Q155.2, Q155.5, R173.1, R174.2
unnamed: Q155.4, Q158.3
unnamed: Q155.6, Q158.1
unnamed: Q156.2, Q156.5, Q165.2, Q165.5, R175.1, R176.2
unnamed: Q156.4, R181.2
unnamed: Q156.6, R182.1
unnamed: Q157.2, Q157.5, Q166.2, Q166.5, R177.1, R178.2
unnamed: Q157.4, R183.2
unnamed: Q157.6, R184.1
unnamed: Q158.2, Q158.5, Q167.2, Q167.5, R179.1, R180.2
unnamed: Q158.4, R185.2
unnamed: Q158.6, R186.1
unnamed: Q159.2, Q159.5, R181.1, R182.2
unnamed: Q159.4, R187.2
unnamed: Q159.6, R188.1
unnamed: Q160.2, Q160.5, R183.1, R184.2
unnamed: Q160.4, R189.2
unnamed: Q160.6, R190.1
unnamed: Q161.2, Q161.5, R185.1, R186.2
unnamed: Q161.4, R191.2
unnamed: Q161.6, R192.1
unnamed: Q162.2, Q162.5, R187.1, R188.2
unnamed: Q162.4, Q165.3
unnamed: Q162.6, Q165.1
unnamed: Q163.2, Q163.5, R189.1, R190.2
unnamed: Q163.4, Q166.3
unnamed: Q163.6, Q166.1
unnamed: Q164.2, Q164.5, R191.1, R192.2
unnamed: Q164.4, Q167.3
unnamed: Q164.6, Q167.1
unnamed: Q165.4, R193.2
unnamed: Q165.6, R194.1
unnamed: Q166.4, R195.2
unnamed: Q166.6, R196.1
unnamed: Q167.4, R197.2
unnamed: Q167.6, R198.1
unnamed: Q168.4, Q177.3
unnamed: Q168.6, Q177.1
unnamed: Q169.4, Q174.4, R199.2
unnamed: Q169.6, Q174.6, R200.1
unnamed: Q170.4, Q178.3
unnamed: Q170.6, Q178.1
unnamed: Q171.4, Q175.4, R201.2
unnamed: Q171.6, Q175.6, R202.1
unnamed: Q172.4, Q179.3
unnamed: Q172.6, Q179.1
unnamed: Q173.4, Q176.4, R203.2
unnamed: Q173.6, Q176.6, R204.1
unnamed: Q174.2, Q174.5, Q177.2, Q177.5, R193.1, R194.2
unnamed: Q175.2, Q175.5, Q178.2, Q178.5, R195.1, R196.2
unnamed: Q176.2, Q176.5, Q179.2, Q179.5, R197.1, R198.2
unnamed: Q177.4, R205.2
unnamed: Q177.6, R206.1
unnamed: Q178.4, R207.2
unnamed: Q178.6, R208.1
unnamed: Q179.4, R209.2
unnamed: Q179.6, R210.1
unnamed: Q180.2, Q180.5, Q198.2, Q198.5, R199.1, R200.2
unnamed: Q180.4, R211.2
unnamed: Q180.6, R212.1
unnamed: Q181.2, Q181.5, Q199.2, Q199.5, R201.1, R202.2
unnamed: Q181.4, R213.2
unnamed: Q181.6, R214.1
unnamed: Q182.2, Q182.5, Q200.2, Q200.5, R203.1, R204.2
unnamed: Q182.4, R215.2
unnamed: Q182.6, R216.1
unnamed: Q183.2, Q183.5, R205.1, R206.2
unnamed: Q183.4, Q186.3
unnamed: Q183.6, Q186.1
unnamed: Q184.2, Q184.5, R207.1, R208.2
unnamed: Q184.4, Q187.3
unnamed: Q184.6, Q187.1
unnamed: Q185.2, Q185.5, R209.1, R210.2
unnamed: Q185.4, Q188.3
unnamed: Q185.6, Q188.1
unnamed: Q186.2, Q186.5, Q195.2, Q195.5, R211.1, R212.2
unnamed: Q186.4, R217.2
unnamed: Q186.6, R218.1
unnamed: Q187.2, Q187.5, Q196.2, Q196.5, R213.1, R214.2
unnamed: Q187.4, R219.2
unnamed: Q187.6, R220.1
unnamed: Q188.2, Q188.5, Q197.2, Q197.5, R215.1, R216.2
unnamed: Q188.4, R221.2
unnamed: Q188.6, R222.1
unnamed: Q189.2, Q189.5, R217.1, R218.2
unnamed: Q189.4, R223.2
unnamed: Q189.6, R224.1
unnamed: Q190.2, Q190.5, R219.1, R220.2
unnamed: Q190.4, R225.2
unnamed: Q190.6, R226.1
unnamed: Q191.2, Q191.5, R221.1, R222.2
unnamed: Q191.4, R227.2
unnamed: Q191.6, R228.1
unnamed: Q192.2, Q192.5, R223.1, R224.2
unnamed: Q192.4, Q195.3
unnamed: Q192.6, Q195.1
unnamed: Q193.2, Q193.5, R225.1, R226.2
unnamed: Q193.4, Q196.3
unnamed: Q193.6, Q196.1
unnamed: Q194.2, Q194.5, R227.1, R228.2
unnamed: Q194.4, Q197.3
unnamed: Q194.6, Q197.1
unnamed: Q195.4, R229.2
unnamed: Q195.6, R230.1
unnamed: Q196.4, R231.2
unnamed: Q196.6, R232.1
unnamed: Q197.4, R233.2
unnamed: Q197.6, R234.1
unnamed: Q198.4, Q201.3
unnamed: Q198.6, Q201.1
unnamed: Q199.4, Q202.3
unnamed: Q199.6, Q202.1
unnamed: Q200.4, Q203.3
unnamed: Q200.6, Q203.1
unnamed: Q201.4, R235.2
unnamed: Q201.6, R236.1
unnamed: Q202.4, R237.2
unnamed: Q202.6, R238.1
unnamed: Q203.4, R239.2
unnamed: Q203.6, R240.1
unnamed: Q204.2, Q204.5, R242.1, R244.2
unnamed: Q204.4, R241.2
unnamed: Q204.6, R243.1
unnamed: Q205.1, Q206.6
unnamed: Q205.4, Q206.4, R242.2
unnamed: Q205.6, R244.1
unnamed: Q207.2, Q207.5, R246.1, R248.2
unnamed: Q207.4, R245.2
unnamed: Q207.6, R247.1
unnamed: Q208.1, Q209.6
unnamed: Q208.4, Q209.4, R246.2
unnamed: Q208.6, R248.1
unnamed: Q210.2, Q210.5, R250.1, R252.2
unnamed: Q210.4, R249.2
unnamed: Q210.6, R251.1
unnamed: Q211.1, Q212.6
unnamed: Q211.4, Q212.4, R250.2
unnamed: Q211.6, R252.1
unnamed: Q213.2, Q213.5, R254.1, R256.2
unnamed: Q213.4, R253.2
unnamed: Q213.6, R255.1
unnamed: Q214.1, Q215.6
unnamed: Q214.4, Q215.4, R254.2
unnamed: Q214.6, R256.1
unnamed: Q216.2, Q216.5, R258.1, R260.2
unnamed: Q216.4, R257.2
unnamed: Q216.6, R259.1
unnamed: Q217.1, Q218.6
unnamed: Q217.4, Q218.4, R258.2
unnamed: Q217.6, R260.1
unnamed: Q219.2, Q219.5, R262.1, R264.2
unnamed: Q219.4, R261.2
unnamed: Q219.6, R263.1
unnamed: Q220.1, Q221.6
unnamed: Q220.4, Q221.4, R262.2
unnamed: Q220.6, R264.1
unnamed: Q222.2, Q222.5, R266.1, R268.2
unnamed: Q222.4, R265.2
unnamed: Q222.6, R267.1
unnamed: Q223.1, Q224.6
unnamed: Q223.4, Q224.4, R266.2
unnamed: Q223.6, R268.1
unnamed: Q225.2, Q225.5, R270.1, R272.2
unnamed: Q225.4, R269.2
unnamed: Q225.6, R271.1
unnamed: Q226.1, Q227.6
unnamed: Q226.4, Q227.4, R270.2
unnamed: Q226.6, R272.1
unnamed: Q228.2, Q228.5, R274.1, R276.2
unnamed: Q228.4, R273.2
unnamed: Q228.6, R275.1
unnamed: Q229.1, Q230.6
unnamed: Q229.4, Q230.4, R274.2
unnamed: Q229.6, R276.1
unnamed: Q231.2, Q231.5, R278.1, R280.2
unnamed: Q231.4, R277.2
unnamed: Q231.6, R279.1
unnamed: Q232.3, Q233.4
unnamed: Q232.4, R278.2
unnamed: Q232.6, Q233.6, R280.1
unnamed: Q234.2, Q234.5, R282.1, R284.2
unnamed: Q234.4, R281.2
unnamed: Q234.6, R283.1
unnamed: Q235.3, Q236.4
unnamed: Q235.4, R282.2
unnamed: Q235.6, Q236.6, R284.1
unnamed: Q237.2, Q237.5, R286.1, R288.2
unnamed: Q237.4, R285.2
unnamed: Q237.6, R287.1
unnamed: Q238.3, Q239.4
unnamed: Q238.4, R286.2
unnamed: Q238.6, Q239.6, R288.1
unnamed: Q240.2, Q240.5, R290.1, R292.2
unnamed: Q240.4, R289.2
unnamed: Q240.6, R291.1
unnamed: Q241.3, Q242.4
unnamed: Q241.4, R290.2
unnamed: Q241.6, Q242.6, R292.1
unnamed: Q243.2, Q243.5, R294.1, R296.2
unnamed: Q243.4, R293.2
unnamed: Q243.6, R295.1
unnamed: Q244.3, Q245.4
unnamed: Q244.4, R294.2
unnamed: Q244.6, Q245.6, R296.1
unnamed: Q246.2, Q246.5, R298.1, R300.2
unnamed: Q246.4, R297.2
unnamed: Q246.6, R299.1
unnamed: Q247.3, Q248.4
unnamed: Q247.4, R298.2
unnamed: Q247.6, Q248.6, R300.1
unnamed: Q249.2, Q249.5, R302.1, R304.2
unnamed: Q249.4, R301.2
unnamed: Q249.6, R303.1
unnamed: Q250.3, Q251.4
unnamed: Q250.4, R302.2
unnamed: Q250.6, Q251.6, R304.1
unnamed: Q252.2, Q252.5, R306.1, R308.2
unnamed: Q252.4, R305.2
unnamed: Q252.6, R307.1
unnamed: Q253.3, Q254.4
unnamed: Q253.4, R306.2
unnamed: Q253.6, Q254.6, R308.1
unnamed: Q255.2, Q255.5, R310.1, R312.2
unnamed: Q255.4, R309.2
unnamed: Q255.6, R311.1
unnamed: Q256.3, Q257.4
unnamed: Q256.4, R310.2
unnamed: Q256.6, Q257.6, R312.1
unnamed: Q258.2, Q258.5, R315.1, R316.2
unnamed: Q258.4, Q259.4, R313.2
unnamed: Q258.6, Q259.6, R314.1
unnamed: Q260.4, R315.2
unnamed: Q260.6, R316.1
unnamed: Q261.2, Q261.5, R319.1, R320.2
unnamed: Q261.4, Q262.4, R317.2
unnamed: Q261.6, Q262.6, R318.1
unnamed: Q263.4, R319.2
unnamed: Q263.6, R320.1
unnamed: Q264.2, Q264.5, R323.1, R324.2
unnamed: Q264.4, Q265.4, R321.2
unnamed: Q264.6, Q265.6, R322.1
unnamed: Q266.4, R323.2
unnamed: Q266.6, R324.1
unnamed: Q267.2, Q267.5, R327.1, R328.2
unnamed: Q267.4, Q268.4, R325.2
unnamed: Q267.6, Q268.6, R326.1
unnamed: Q269.4, R327.2
unnamed: Q269.6, R328.1
unnamed: Q270.2, Q270.5, R331.1, R332.2
unnamed: Q270.4, Q271.4, R329.2
unnamed: Q270.6, Q271.6, R330.1
unnamed: Q272.4, R331.2
unnamed: Q272.6, R332.1
unnamed: Q273.2, Q273.5, R335.1, R336.2
unnamed: Q273.4, Q274.4, R333.2
unnamed: Q273.6, Q274.6, R334.1
unnamed: Q275.4, R335.2
unnamed: Q275.6, R336.1
unnamed: Q276.2, Q276.5, R339.1, R340.2
unnamed: Q276.4, Q277.4, R337.2
unnamed: Q276.6, Q277.6, R338.1
unnamed: Q278.4, R339.2
unnamed: Q278.6, R340.1
unnamed: Q279.2, Q279.5, R343.1, R344.2
unnamed: Q279.4, Q280.4, R341.2
unnamed: Q279.6, Q280.6, R342.1
unnamed: Q281.4, R343.2
unnamed: Q281.6, R344.1
unnamed: Q282.2, Q282.5, R347.1, R348.2
unnamed: Q282.4, Q283.4, R345.2
unnamed: Q282.6, Q283.6, R346.1
unnamed: Q284.4, R347.2
unnamed: Q284.6, R348.1
unnamed: Q285.2, Q285.5, R350.1, R352.2
unnamed: Q285.4, R349.2
unnamed: Q285.6, R351.1
unnamed: Q286.4, Q287.4, R350.2
unnamed: Q286.6, Q287.6, R352.1
unnamed: Q288.2, Q288.5, R354.1, R356.2
unnamed: Q288.4, R353.2
unnamed: Q288.6, R355.1
unnamed: Q289.4, Q290.4, R354.2
unnamed: Q289.6, Q290.6, R356.1
unnamed: Q291.2, Q291.5, R358.1, R360.2
unnamed: Q291.4, R357.2
unnamed: Q291.6, R359.1
unnamed: Q292.4, Q293.4, R358.2
unnamed: Q292.6, Q293.6, R360.1
unnamed: Q294.2, Q294.5, R362.1, R364.2
unnamed: Q294.4, R361.2
unnamed: Q294.6, R363.1
unnamed: Q295.4, Q296.4, R362.2
unnamed: Q295.6, Q296.6, R364.1
unnamed: Q297.2, Q297.5, R366.1, R368.2
unnamed: Q297.4, R365.2
unnamed: Q297.6, R367.1
unnamed: Q298.4, Q299.4, R366.2
unnamed: Q298.6, Q299.6, R368.1
unnamed: Q300.2, Q300.5, R370.1, R372.2
unnamed: Q300.4, R369.2
unnamed: Q300.6, R371.1
unnamed: Q301.4, Q302.4, R370.2
unnamed: Q301.6, Q302.6, R372.1
unnamed: Q303.2, Q303.5, R374.1, R376.2
unnamed: Q303.4, R373.2
unnamed: Q303.6, R375.1
unnamed: Q304.4, Q305.4, R374.2
unnamed: Q304.6, Q305.6, R376.1
unnamed: Q306.2, Q306.5, R378.1, R380.2
unnamed: Q306.4, R377.2
unnamed: Q306.6, R379.1
unnamed: Q307.4, Q308.4, R378.2
unnamed: Q307.6, Q308.6, R380.1
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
